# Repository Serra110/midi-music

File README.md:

# MIDI Keypad

This project is a custom MIDI controller inspired by Kai Pereira's [MIDI Keypad project](https://github.com/KaiPereira/MIDI-Keypad). It uses a Raspberry Pi Pico to turn physical controls into MIDI input. My version adapts the original design to use the Raspberry Pi Pico and combines buttons, touch-sensitive keys, a rotary encoder and slide potentiometers to provide different ways to control MIDI instruments and software.

## Hardware Design

The controller is designed with the Raspberry Pi Pico, which reads the inputs from the different controls and handles the MIDI functionality. The design includes three physical keys, seven capacitive touch inputs, two Bourns slide potentiometers and a rotary encoder, providing a combination of digital and analog controls.

### 3D Model

A 3D representation of the controller designed in KiCad.

### Schematic

## Controls

The controller includes several types of input:

- **Physical keys:** Three buttons for triggering assigned actions.
- **Capacitive touch keys:** Seven touch-sensitive inputs for triggering MIDI actions.
- **Bourns slide potentiometers:** Two sliders for controlling continuous MIDI parameters.
- **Rotary encoder:** A rotational control for navigating values or adjusting parameters.

## Code

The firmware runs on the Raspberry Pi Pico and reads the connected controls to handle their inputs and MIDI functionality. The aim is to use the controller as a physical interface for music software, with the different controls offering flexible ways to trigger notes and adjust parameters.

## About the Project
it is my first music related pcb and i am really grateful to be given the chance to learn this 
Also, the placement of the capacitive touch keys are placed like that due to being easier to use with 2 hands using the thumb, without needing to loom at the keys, being easily touched without much movement

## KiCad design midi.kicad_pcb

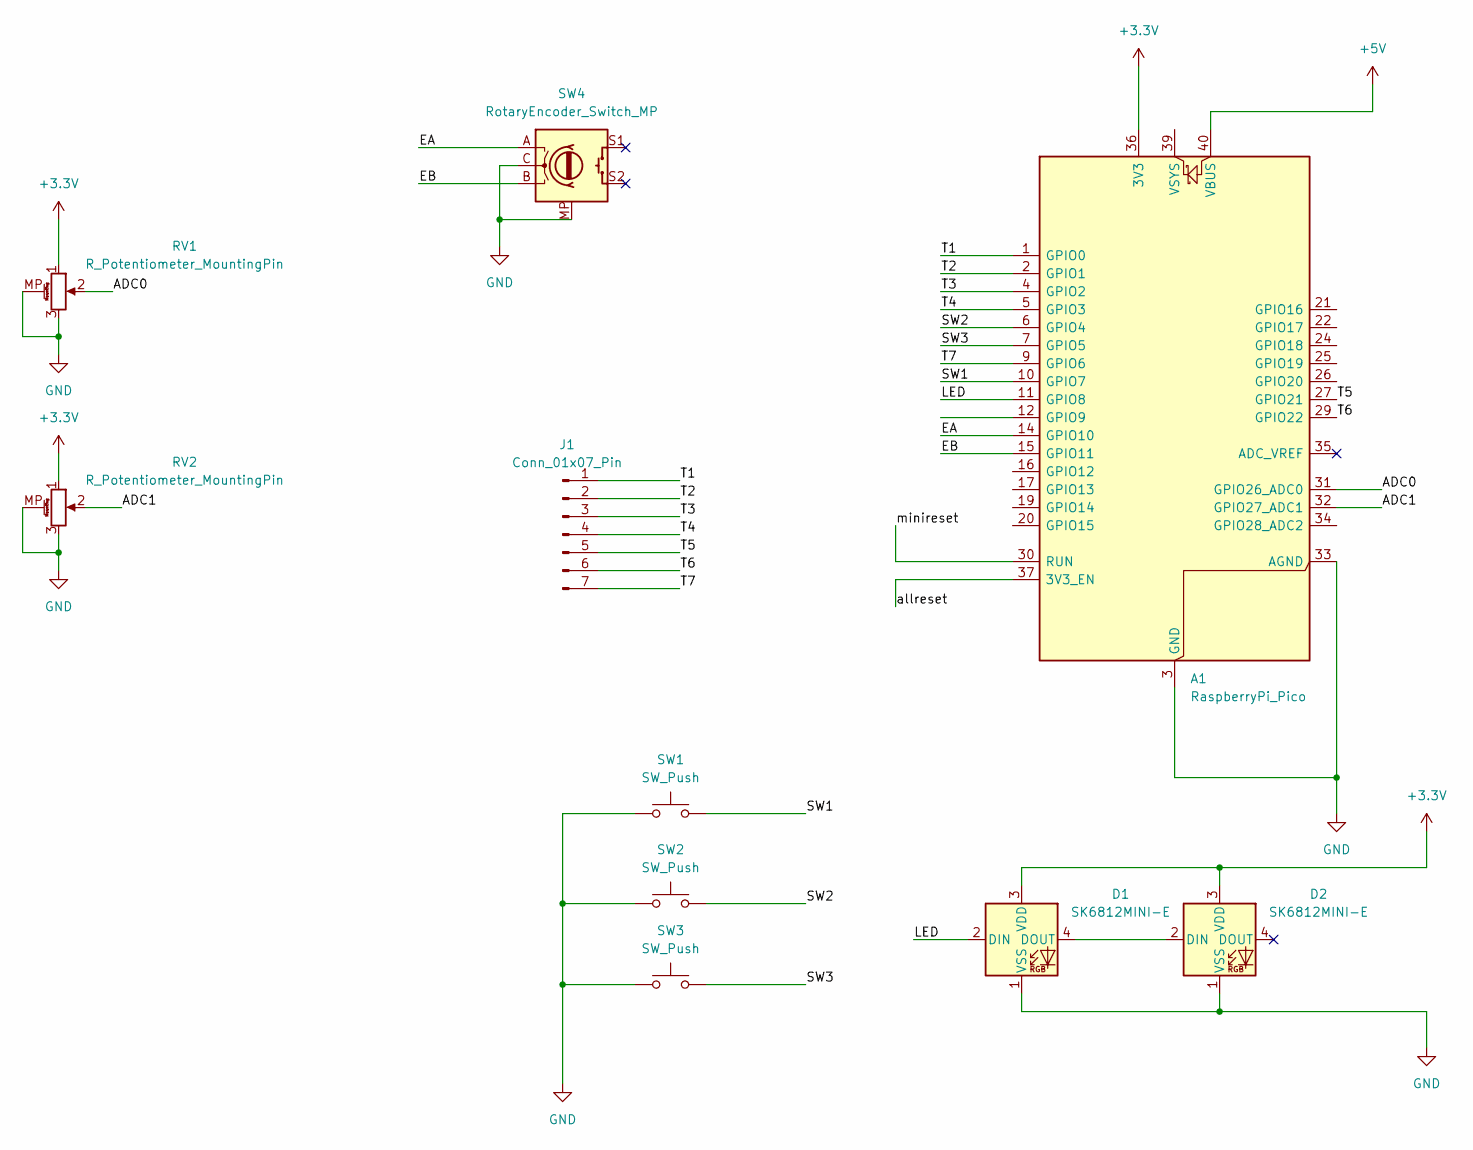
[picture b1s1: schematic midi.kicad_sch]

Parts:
A1: RaspberryPi_Pico; RaspberryPi_Pico_Common
D1, D2: SK6812MINI-E; LED_SK6812MINI-E_3.2x2.8mm_P1.5mm_ReverseMount
J1: Conn_01x07_Pin; Untitled
RV1, RV2: R_Potentiometer_MountingPin; Potentiometer_Bourns_PTA1543_Single_Slide
SW1, SW2, SW3: SW_Push; SW_Cherry_MX_1.00u_PCB
SW4: RotaryEncoder_Switch_MP; RotaryEncoder_Alps_EC11E-Switch_Vertical_H20mm

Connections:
+3.3V: A1.36 (3V3), D1.3 (VDD), D2.3 (VDD), RV1.1, RV2.1
+5V: A1.40 (VBUS)
/ADC0: A1.31 (GPIO26_ADC0), RV1.2
/ADC1: A1.32 (GPIO27_ADC1), RV2.2
/EA: A1.14 (GPIO10), SW4.A
/EB: A1.15 (GPIO11), SW4.B
/LED: A1.11 (GPIO8), D1.2 (DIN)
/SW1: A1.10 (GPIO7), SW1.2
/SW2: A1.6 (GPIO4), SW2.2
/SW3: A1.7 (GPIO5), SW3.2
/T1: A1.1 (GPIO0), J1.1
/T2: A1.2 (GPIO1), J1.2
/T3: A1.4 (GPIO2), J1.3
/T4: A1.5 (GPIO3), J1.4
/T5: A1.27 (GPIO21), J1.5
/T6: A1.29 (GPIO22), J1.6
/T7: A1.9 (GPIO6), J1.7
/allreset: A1.37 (3V3_EN)
/minireset: A1.30 (RUN)
GND: A1.3 (GND), A1.8 (GND), A1.13 (GND), A1.18 (GND), A1.23 (GND), A1.28 (GND), A1.33 (AGND), A1.38 (GND), D1.1 (VSS), D2.1 (VSS), RV1.3, RV1.MP (MountPin), RV2.3, RV2.MP (MountPin), SW1.1, SW2.1, SW3.1, SW4.C, SW4.MP
unnamed: D1.4 (DOUT), D2.2 (DIN)

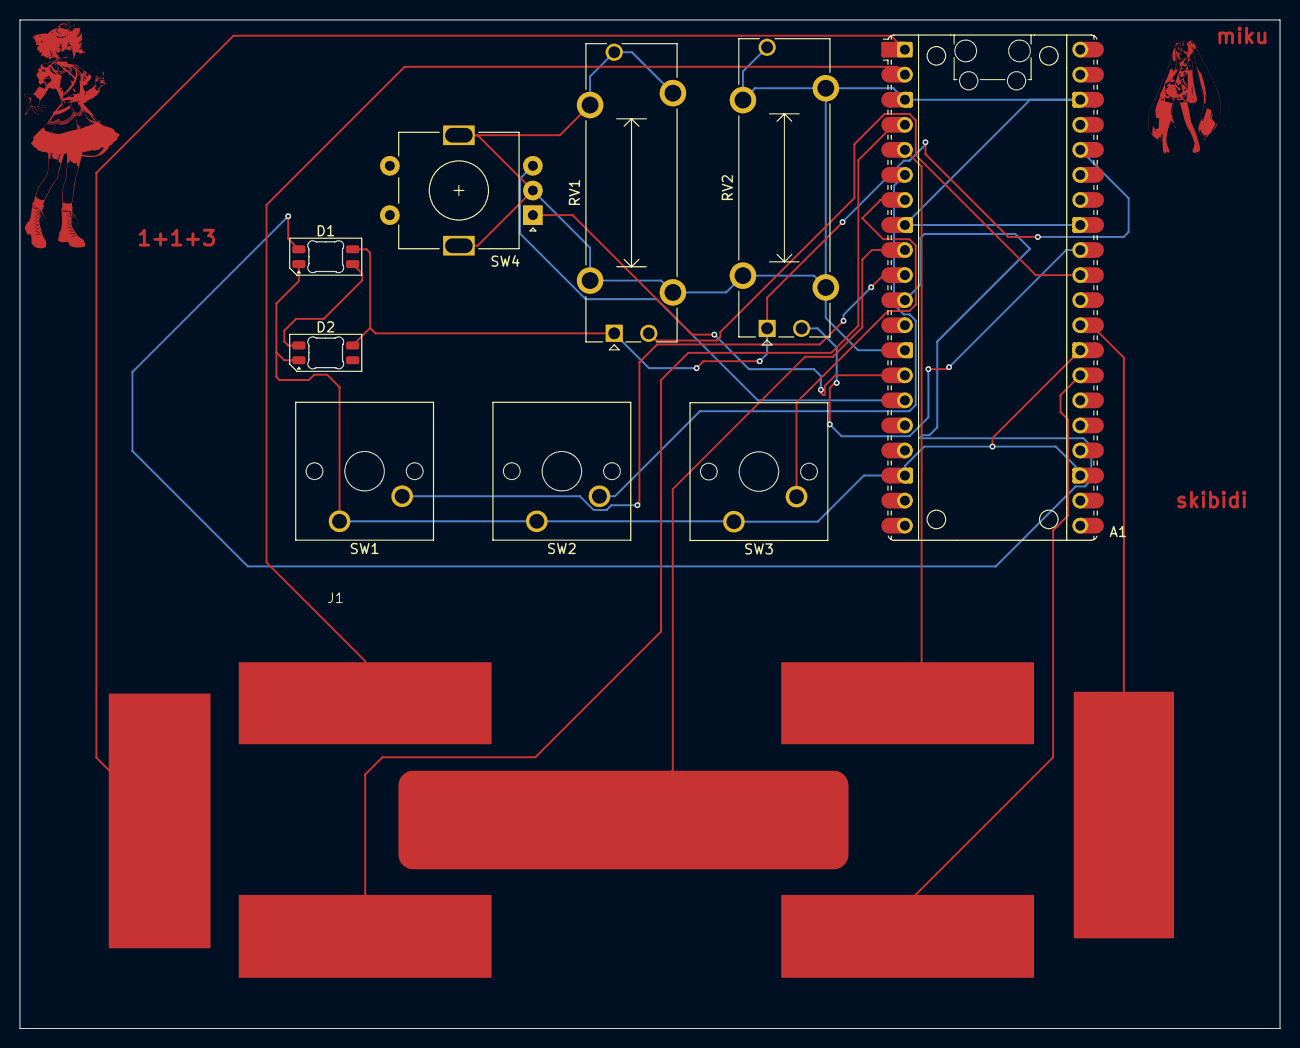
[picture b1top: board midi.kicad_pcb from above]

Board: 2 copper layers, 127.8 x 102.2 mm, 10 parts (0 on the bottom side), 18 nets.

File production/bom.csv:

Designator,Footprint,Quantity,Value,LCSC Part #
A1,RaspberryPi_Pico_Common,1,RaspberryPi_Pico,
"D1, D2",LED_SK6812MINI-E_3.2x2.8mm_P1.5mm_ReverseMount,2,SK6812MINI-E,
J1,Untitled,1,Conn_01x07_Pin,
"RV1, RV2",Potentiometer_Bourns_PTA1543_Single_Slide,2,R_Potentiometer_MountingPin,
"SW1, SW2, SW3",SW_Cherry_MX_1.00u_PCB,3,SW_Push,
SW4,RotaryEncoder_Alps_EC11E-Switch_Vertical_H20mm,1,RotaryEncoder_Switch_MP,
